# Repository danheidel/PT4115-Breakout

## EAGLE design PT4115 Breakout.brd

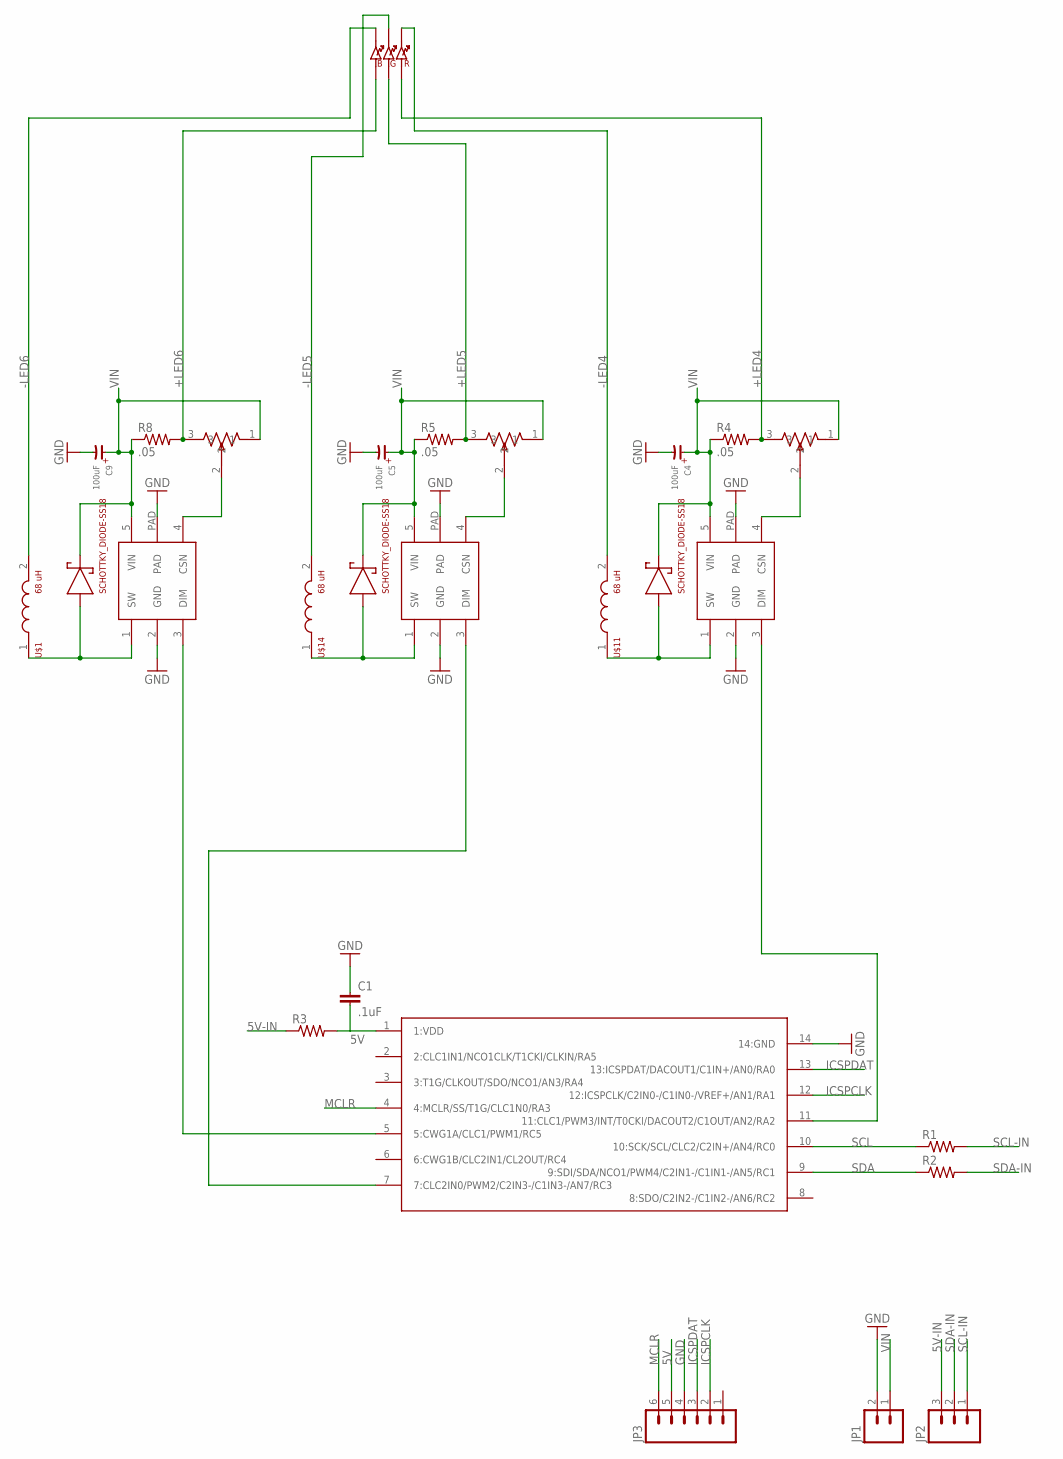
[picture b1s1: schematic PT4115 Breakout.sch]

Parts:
C1: .1uF; 0805
C4, C5, C9: 100uF; 8MMCAP
JP1: M02LOCK; 1X02_LOCK
JP2: M03LOCK; 1X03_LOCK
JP3: M06LOCK; 1X06_LOCK
R1, R2, R3: RESISTOR; 0805
R4, R5, R8: .05; 1206
U$1, U$11, U$14: 68 uH; VLF10040
U$4: BIGRGB
U$5: PIC16F1503TSSOP14; TSSOP14
U$8, U$9, U$10: TRIMPOTTC33X-2; TC33X-2
U$12, U$15, U$23: SCHOTTKY_DIODE-SS18; DO-214
U$13, U$16, U$24: PT4115; SOT89-5

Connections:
5V: C1.2, JP3.5, R3.2, U$5.1 (1:VDD)
5V-IN: JP2.3, R3.1
+LED4: R4.2, U$4.R+, U$10.3
+LED5: R5.2, U$4.G+, U$9.3
+LED6: R8.2, U$4.B+, U$8.3
-LED4: U$4.R-, U$11.2
-LED5: U$4.G-, U$14.2
-LED6: U$1.2, U$4.B-
GND: C1.1, C4.-, C5.-, C9.-, JP1.2, JP3.4, U$5.14 (14:GND), U$13.2 (GND), U$13.PAD, U$16.2 (GND), U$16.PAD, U$24.2 (GND), U$24.PAD
ICSPCLK: JP3.2, U$5.12 (12:ICSPCLK/C2IN0-/C1IN0-/VREF+/AN1/RA1)
ICSPDAT: JP3.3, U$5.13 (13:ICSPDAT/DACOUT1/C1IN+/AN0/RA0)
MCLR: JP3.6, U$5.4 (4:MCLR/SS/T1G/CLC1N0/RA3)
unnamed: U$5.5 (5:CWG1A/CLC1/PWM1/RC5), U$24.3 (DIM)
unnamed: U$5.7 (7:CLC2IN0/PWM2/C2IN3-/C1IN3-/AN7/RC3), U$16.3 (DIM)
unnamed: U$5.11 (11:CLC1/PWM3/INT/T0CKI/DACOUT2/C1OUT/AN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), U$13.3 (DIM)
unnamed: U$8.2, U$24.4 (CSN)
unnamed: U$9.2, U$16.4 (CSN)
unnamed: U$10.2, U$13.4 (CSN)
SCL: R1.1, U$5.10 (10:SCK/SCL/CLC2/C2IN+/AN4/RC0)
SCL-IN: JP2.1, R1.2
SDA: R2.1, U$5.9 (9:SDI/SDA/NCO1/PWM4/C2IN1-/C1IN1-/AN5/R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)
SDA-IN: JP2.2, R2.2
SW4: U$11.1, U$12.P$2 (ANODE), U$13.1 (SW)
SW5: U$14.1, U$15.P$2 (ANODE), U$16.1 (SW)
SW6: U$1.1, U$23.P$2 (ANODE), U$24.1 (SW)
VIN: C4.+, C5.+, C9.+, JP1.1, R4.1, R5.1, R8.1, U$8.1, U$9.1, U$10.1, U$12.P$1 (CATHODE), U$13.5 (VIN), U$15.P$1 (CATHODE), U$16.5 (VIN), U$23.P$1 (CATHODE), U$24.5 (VIN)

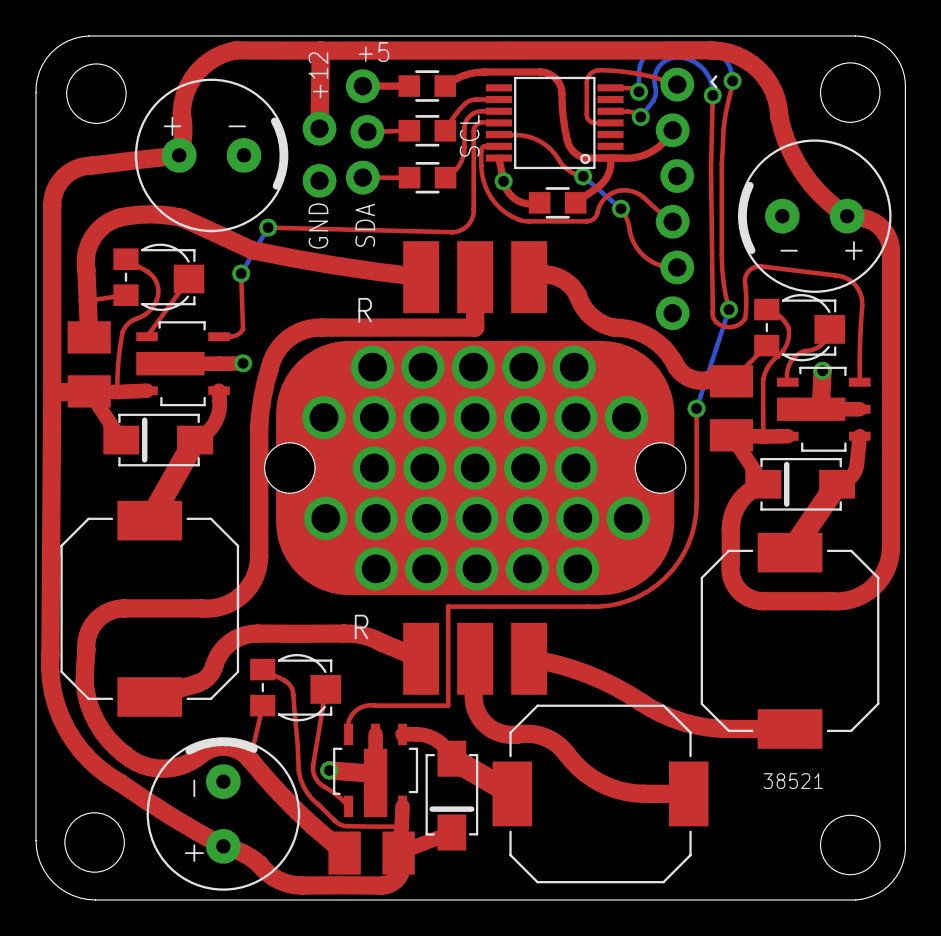
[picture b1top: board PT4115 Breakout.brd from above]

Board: 2 copper layers, 48.3 x 48.0 mm, 31 parts (0 on the bottom side), 26 nets.

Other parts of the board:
U$2, U$3, U$6, U$7: STAND-OFF

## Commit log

2011-07-25 Mostly done...
2011-08-19 Shrank the board a bit
2011-09-26 Minor library edits, rounded corners
2011-09-26 Added mounting holes
2011-09-26 Rerouted signal path around mounting hole for more clearance
2011-11-03 Changed to use pic chip and I2C communication
2011-11-08 Added trimpots
2011-11-08 CAM files
2011-11-08 layer tweaks
2011-11-22 Added potentiometers
2011-12-24 deleted Eagle backup files
2012-03-05 minor edits
2012-03-16 Updated .eps for smaller pads.
2012-03-17 Added paste .eps file.
2012-04-26 .eps tweaks
2012-05-22 Lots of minor tweaks
    PIC programming header moved to get clearance around capacitor.
    Some components moved to improve soldering ease.
